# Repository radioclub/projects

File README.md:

# radio-projects
Projects for Radio Club

## Requirements
Projects require a KiCad version of at least 8.0

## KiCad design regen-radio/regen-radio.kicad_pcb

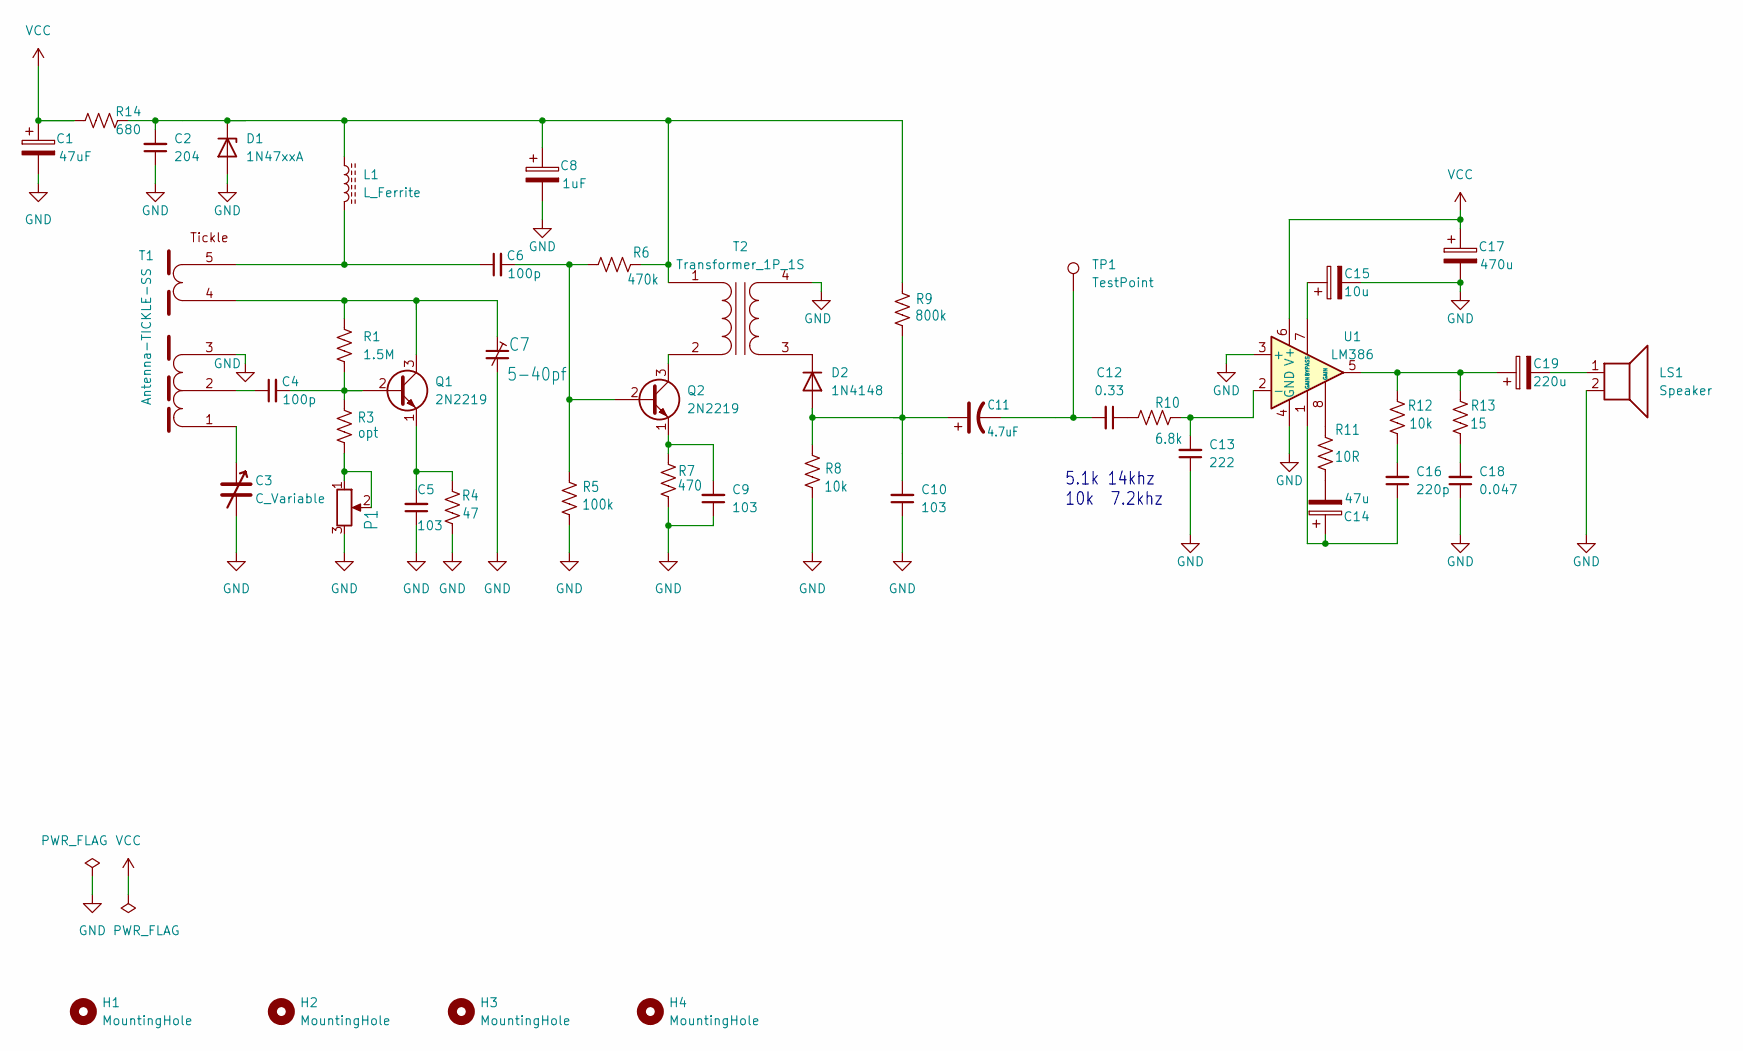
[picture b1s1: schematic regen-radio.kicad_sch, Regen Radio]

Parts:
C1: 47uF; CP_Radial_D8.0mm_P5.00mm
C2: 204; C_Disc_D10.0mm_W2.5mm_P5.00mm
C3: C_Variable; SolderWire-0.75sqmm_1x02_P4.8mm_D1.25mm_OD2.3mm_Relief
C4, C6: 100p; C_Disc_D10.0mm_W2.5mm_P5.00mm
C5, C9, C10: 103; C_Disc_D10.0mm_W2.5mm_P5.00mm
C7: 5-40pf; Film-C-Trimmer-PTH-D7.5-P5.08-3
C8: 1uF; CP_Radial_D8.0mm_P5.00mm
C11: 4.7uF; CP_Radial_D8.0mm_P5.00mm
C12: 0.33; C_Disc_D10.0mm_W2.5mm_P5.00mm
C13: 222; C_Disc_D10.0mm_W2.5mm_P5.00mm
C14: 47u; CP_Radial_D8.0mm_P5.00mm
C15: 10u; CP_Radial_D8.0mm_P5.00mm
C16: 220p; C_Disc_D10.0mm_W2.5mm_P5.00mm
C17: 470u; CP_Radial_D8.0mm_P5.00mm
C18: 0.047; C_Disc_D10.0mm_W2.5mm_P5.00mm
C19: 220u; CP_Radial_D8.0mm_P5.00mm
D1: 1N47xxA; D_DO-41_SOD81_P10.16mm_Horizontal
D2: 1N4148; D_DO-35_SOD27_P7.62mm_Horizontal
H1, H2, H3, H4: MountingHole; MountingHole_2.2mm_M2_Pad_Via
L1: L_Ferrite; L_Toroid_Vertical_L13.0mm_W6.5mm_P5.60mm
LS1: Speaker; SolderWire-0.5sqmm_1x02_P4.6mm_D0.9mm_OD2.1mm
P1: POTWS20; Potentiometer_Bourns_3339P_Vertical_HandSoldering
Q1, Q2: 2N2219; TO-39-3
R1: 1.5M; C_Disc_D10.0mm_W2.5mm_P5.00mm
R3: opt; R_Axial_DIN0411_L9.9mm_D3.6mm_P12.70mm_Horizontal
R4: 47; R_Axial_DIN0411_L9.9mm_D3.6mm_P12.70mm_Horizontal
R5: 100k; R_Axial_DIN0411_L9.9mm_D3.6mm_P12.70mm_Horizontal
R6: 470k; R_Axial_DIN0411_L9.9mm_D3.6mm_P12.70mm_Horizontal
R7: 470; R_Axial_DIN0411_L9.9mm_D3.6mm_P12.70mm_Horizontal
R8, R12: 10k; R_Axial_DIN0411_L9.9mm_D3.6mm_P12.70mm_Horizontal
R9: 800k; R_Axial_DIN0411_L9.9mm_D3.6mm_P12.70mm_Horizontal
R10: 6.8k; R_Axial_DIN0411_L9.9mm_D3.6mm_P12.70mm_Horizontal
R11: 10R; R_Axial_DIN0411_L9.9mm_D3.6mm_P12.70mm_Horizontal
R13: 15; R_Axial_DIN0411_L9.9mm_D3.6mm_P12.70mm_Horizontal
R14: 680; C_Disc_D10.0mm_W2.5mm_P5.00mm
T1: Antenna-TICKLE-SS; SolderWire-0.1sqmm_1x05_P3.6mm_D0.4mm_OD1mm_Relief
T2: Transformer_1P_1S; FT50-43-Bifilar
TP1: TestPoint; TestPoint_Loop_D2.50mm_Drill1.0mm
U1: LM386; DIP-8_W7.62mm_Socket_LongPads

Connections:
GND: C1.2, C2.1, C3.2, C5.1, C7.2, C8.2, C9.1, C10.1, C13.1, C15.2, C17.2, C18.1, D1.2 (A), LS1.2, P1.3, R4.2, R5.2, R7.2, R8.2, T1.3 (SB), T2.4 (SB), U1.3 (+), U1.4 (GND)
unnamed: C11.2, C12.2, TP1.1
unnamed: C12.1, R10.1
unnamed: C14.1, C16.1, U1.1 (GAIN)
unnamed: C14.2, R11.1
unnamed: C16.2, R12.2
unnamed: C18.2, R13.2
unnamed: C19.1, R12.1, R13.1, U1.5
unnamed: C19.2, LS1.1
unnamed: C2.2, C8.1, D1.1 (K), L1.1, R6.1, R9.1, R14.2, T2.1 (AA)
unnamed: C10.2, C11.1, D2.2 (A), R8.1, R9.2
unnamed: D2.1 (K), T2.3 (SA)
unnamed: P1.1, P1.2, R3.2
unnamed: C4.2, Q1.2 (B), R1.1, R3.1
unnamed: C7.1, Q1.3 (C), R1.2, T1.4 (Tick2)
unnamed: C5.2, Q1.1 (E), R4.1
unnamed: C6.2, Q2.2 (B), R5.1, R6.2
unnamed: Q2.3 (C), T2.2 (AB)
unnamed: C9.2, Q2.1 (E), R7.1
unnamed: R11.2, U1.8 (GAIN)
unnamed: C3.1, T1.1 (SA)
unnamed: C4.1, T1.2 (SC)
unnamed: C6.1, L1.2, T1.5 (Tick1)
unnamed: C13.2, R10.2, U1.2 (-)
unnamed: C15.1, U1.7 (BYPASS)
VCC: C1.1, C17.1, R14.1, U1.6 (V+)

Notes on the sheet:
5.1k 14khz 10k 7.2khz

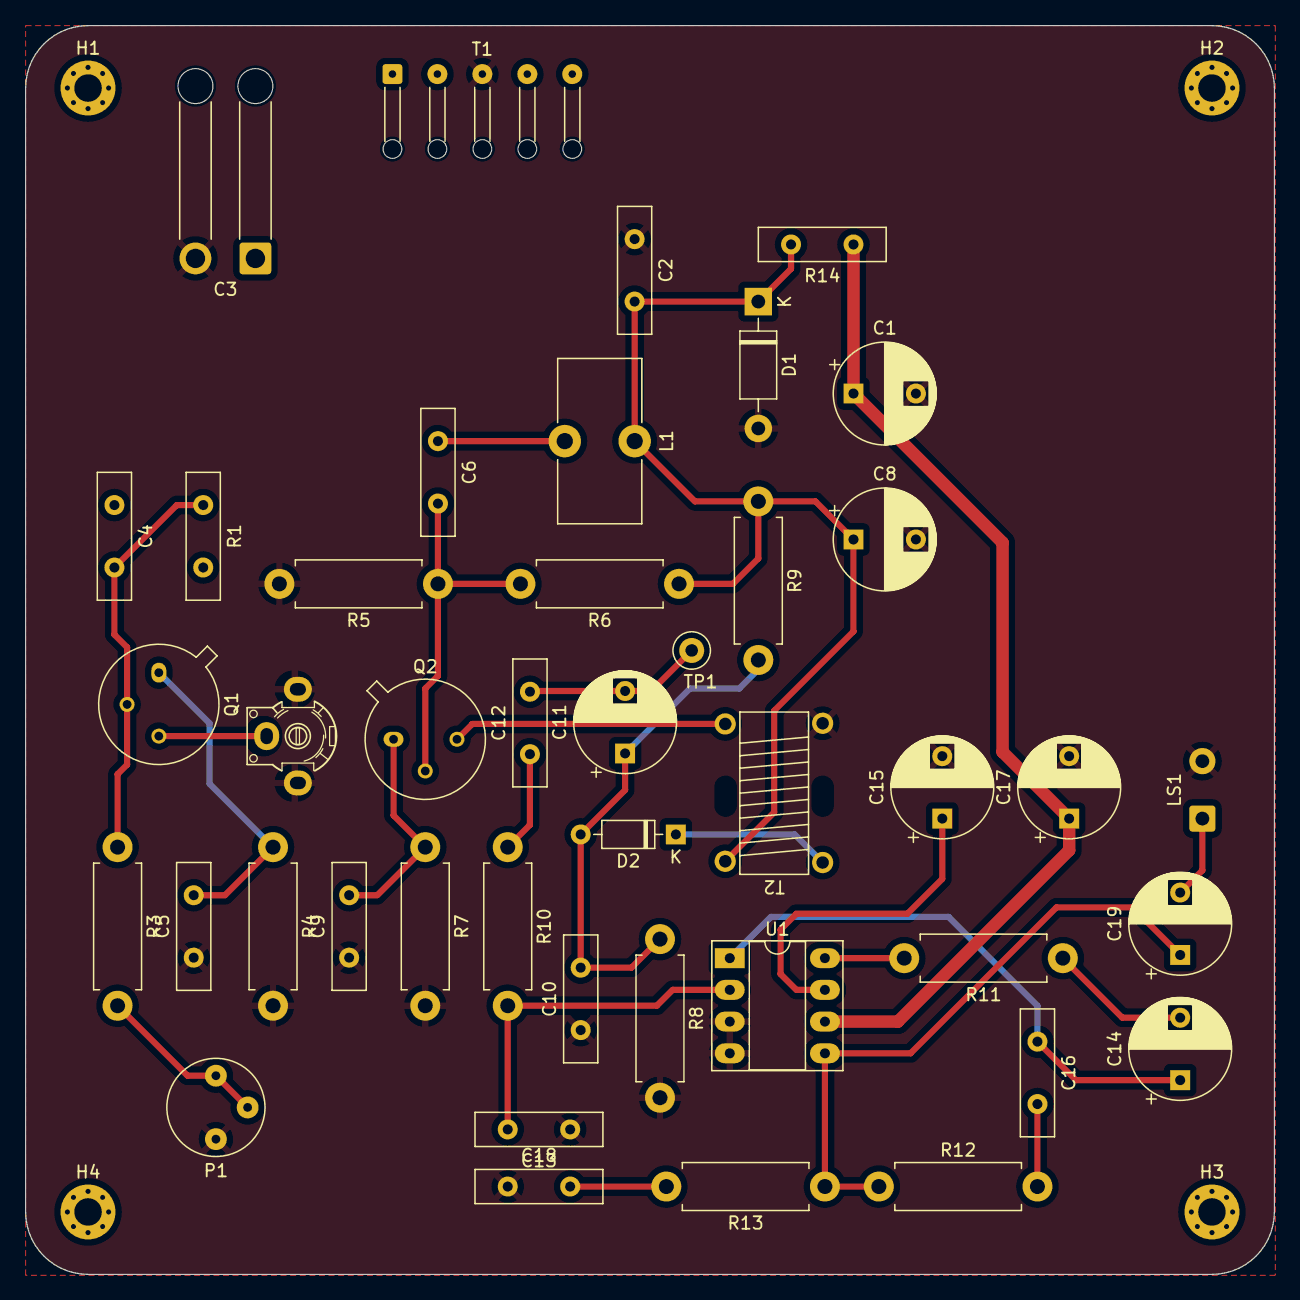
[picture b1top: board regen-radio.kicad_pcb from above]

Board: 2 copper layers, 100.0 x 100.0 mm, 47 parts (0 on the bottom side), 26 nets.

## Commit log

2024-01-25 init(regen-radio): init project
2024-01-25 feat(regen-radio): add library submodule
2024-01-25 feat: regen radio schematic
2024-01-28 feat(regen-radio): add sch meta
2024-02-01 chore(regen-radio): clean up labels
2024-02-01 feat(regen-radio): assign most footprints to sch
2024-02-01 fix: relative lib path
2024-02-01 fix: update library
2024-02-01 fix: assign missing footprints
2024-02-01 fix: ignore lockfiles
2024-02-01 feat(regen-radio): basic footprint placement
2024-02-25 chore: update project files to KiCad 8
2024-02-25 chore: update project requirements in README
2024-02-25 chore: update library
2024-03-02 feat: basic layout
